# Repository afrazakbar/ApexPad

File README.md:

# ApexPad

***ApexPad*** is a *minimal* 4-key + encoder **HackPad** mainly designed for **video editing**. It features an OLED display and uses the **QMK Firmware Framework**.

---

## Features

* OLED display with startup animations and more
* 2-part case
* Pookie-sized
* 4 macro keys
* Rotary encoder for volume control
* QMK-powered firmware
* Compact PCB design

---

## CAD Model

Made in **Tinkercad**. I got tired of fighting with Fusion 360 and switched to Tinkercad. 

---

## PCB

### Schematic

### PCB Layout

---

## Firmware Overview

This HackPad uses **QMK Firmware**.

| Control        | Function                              |
| -------------- | ------------------------------------- |
| **SW1**        | Copy (`Ctrl+C`)                       |
| **SW2**        | Paste (`Ctrl+V`)                      |
| **SW3**        | Undo (`Ctrl+Z`)                       |
| **SW4**        | Split (`Ctrl+B`, assigned for CapCut) |
| **Encoder SW** | Redo (`Ctrl+Shift+Z`)                 |
| **Encoder**    | Volume Up / Down                      |

And that's it. I might add something else later. 👀

---

## BOM

Everything you need to build this HackPad:

| Quantity | Component                    |
| -------: | ---------------------------- |
|       1× | Seeed Studio XIAO RP2040     |
|       4× | DSA keycaps                  |
|       4× | MX-style mechanical switches |
|       1× | 0.91" 128×32 OLED display    |
|       1× | EC11 rotary encoder          |
|       8× | M3 screws                    |
|       8× | M3 heat-set inserts          |
|       1× | 2-part printed case          |

---

## Software

* **QMK Firmware**
* **Tinkercad** for the CAD model
* **KiCad** for PCB design

## Hardware

* Seeed Studio XIAO RP2040
* 4× mechanical switches
* EC11 rotary encoder
* 0.91" 128×32 SSD1306 OLED
* Custom PCB
* Custom 2-part 3D-printed case

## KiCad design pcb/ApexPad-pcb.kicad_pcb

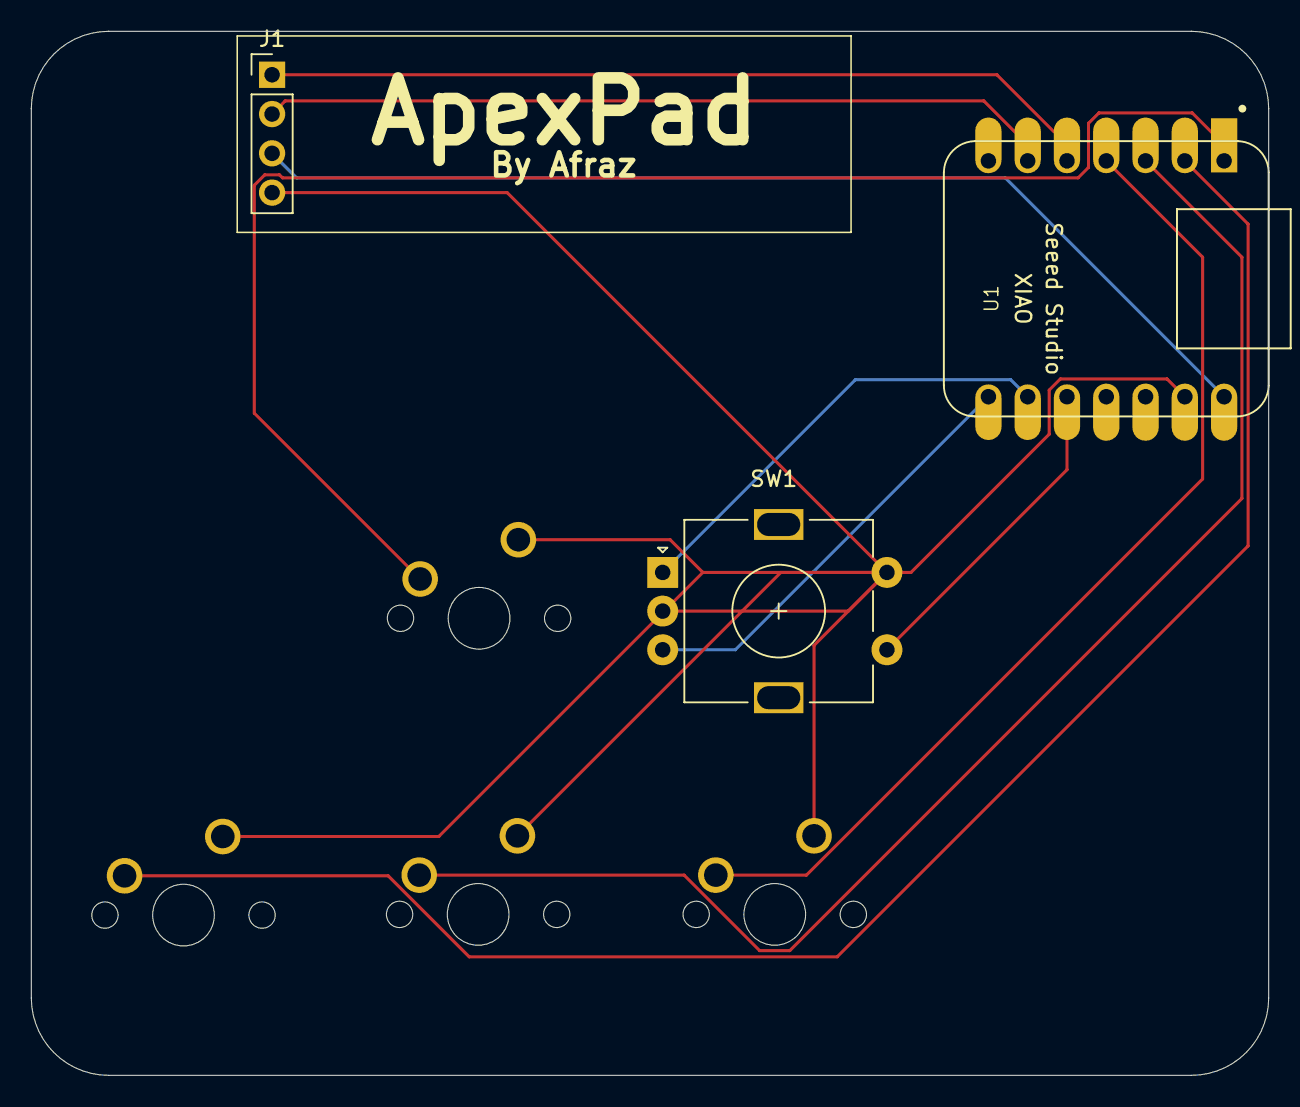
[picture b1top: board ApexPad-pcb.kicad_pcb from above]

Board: 2 copper layers, 80.0 x 67.5 mm, 7 parts (0 on the bottom side), 11 nets.

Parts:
J1: OLED_DISPLAY; PinHeader_1x04_P2.54mm_Vertical
SW1: RotaryEncoder_Switch; RotaryEncoder_Alps_EC11E-Switch_Vertical_H20mm
SW2, SW3, SW4, SW5: SW_Push_45deg; MX-Solderable-1U
U1: Seeed Studio XIAO RP2040; XIAO-Generic-Hybrid-14P-2.54-21X17.8MM

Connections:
EC11A: SW1.A, U1.9 (PA7_A8_D8_SCK)
EC11B: SW1.B, U1.8 (PB09_A7_D7_RX)
EC11SWB: SW1.S1, U1.10 (PA5_A9_D9_MISO)
GND: J1.4, SW1.C, SW1.S2, SW2.2, SW3.2, SW4.2, SW5.2, U1.13 (GND)
SCL: J1.2, U1.6 (PA9_A5_D5_SCL)
SDA: J1.1, U1.5 (PA8_A4_D4_SDA)
SW2: SW2.1, U1.1 (PA02_A0_D0)
SW3: SW3.1, U1.2 (PA4_A1_D1)
SW4: SW4.1, U1.3 (PA10_A2_D2)
SW5: SW5.1, U1.4 (PA11_A3_D3)
VCC: J1.3, U1.14 (5V)
